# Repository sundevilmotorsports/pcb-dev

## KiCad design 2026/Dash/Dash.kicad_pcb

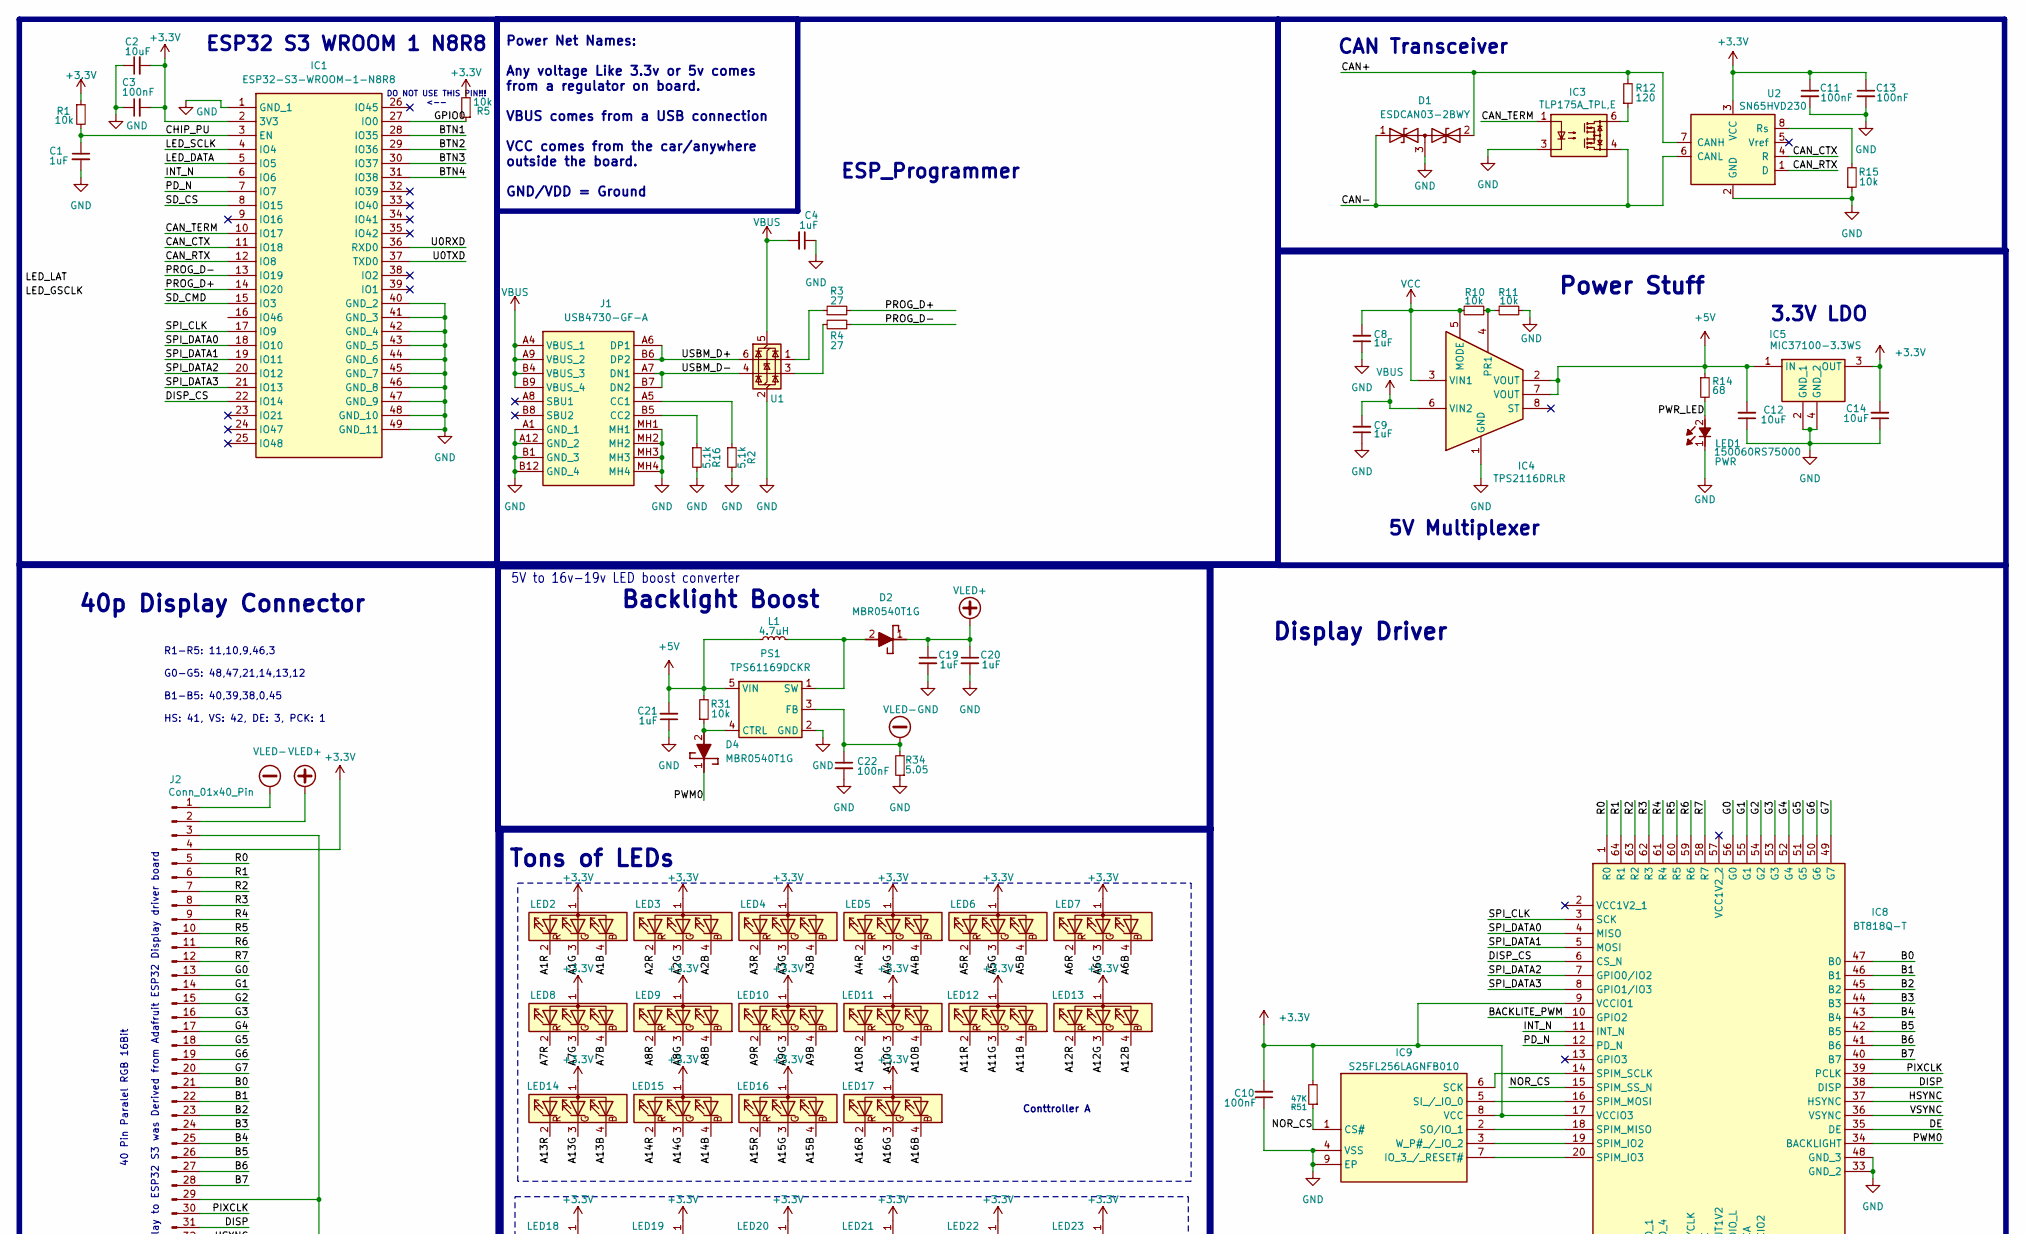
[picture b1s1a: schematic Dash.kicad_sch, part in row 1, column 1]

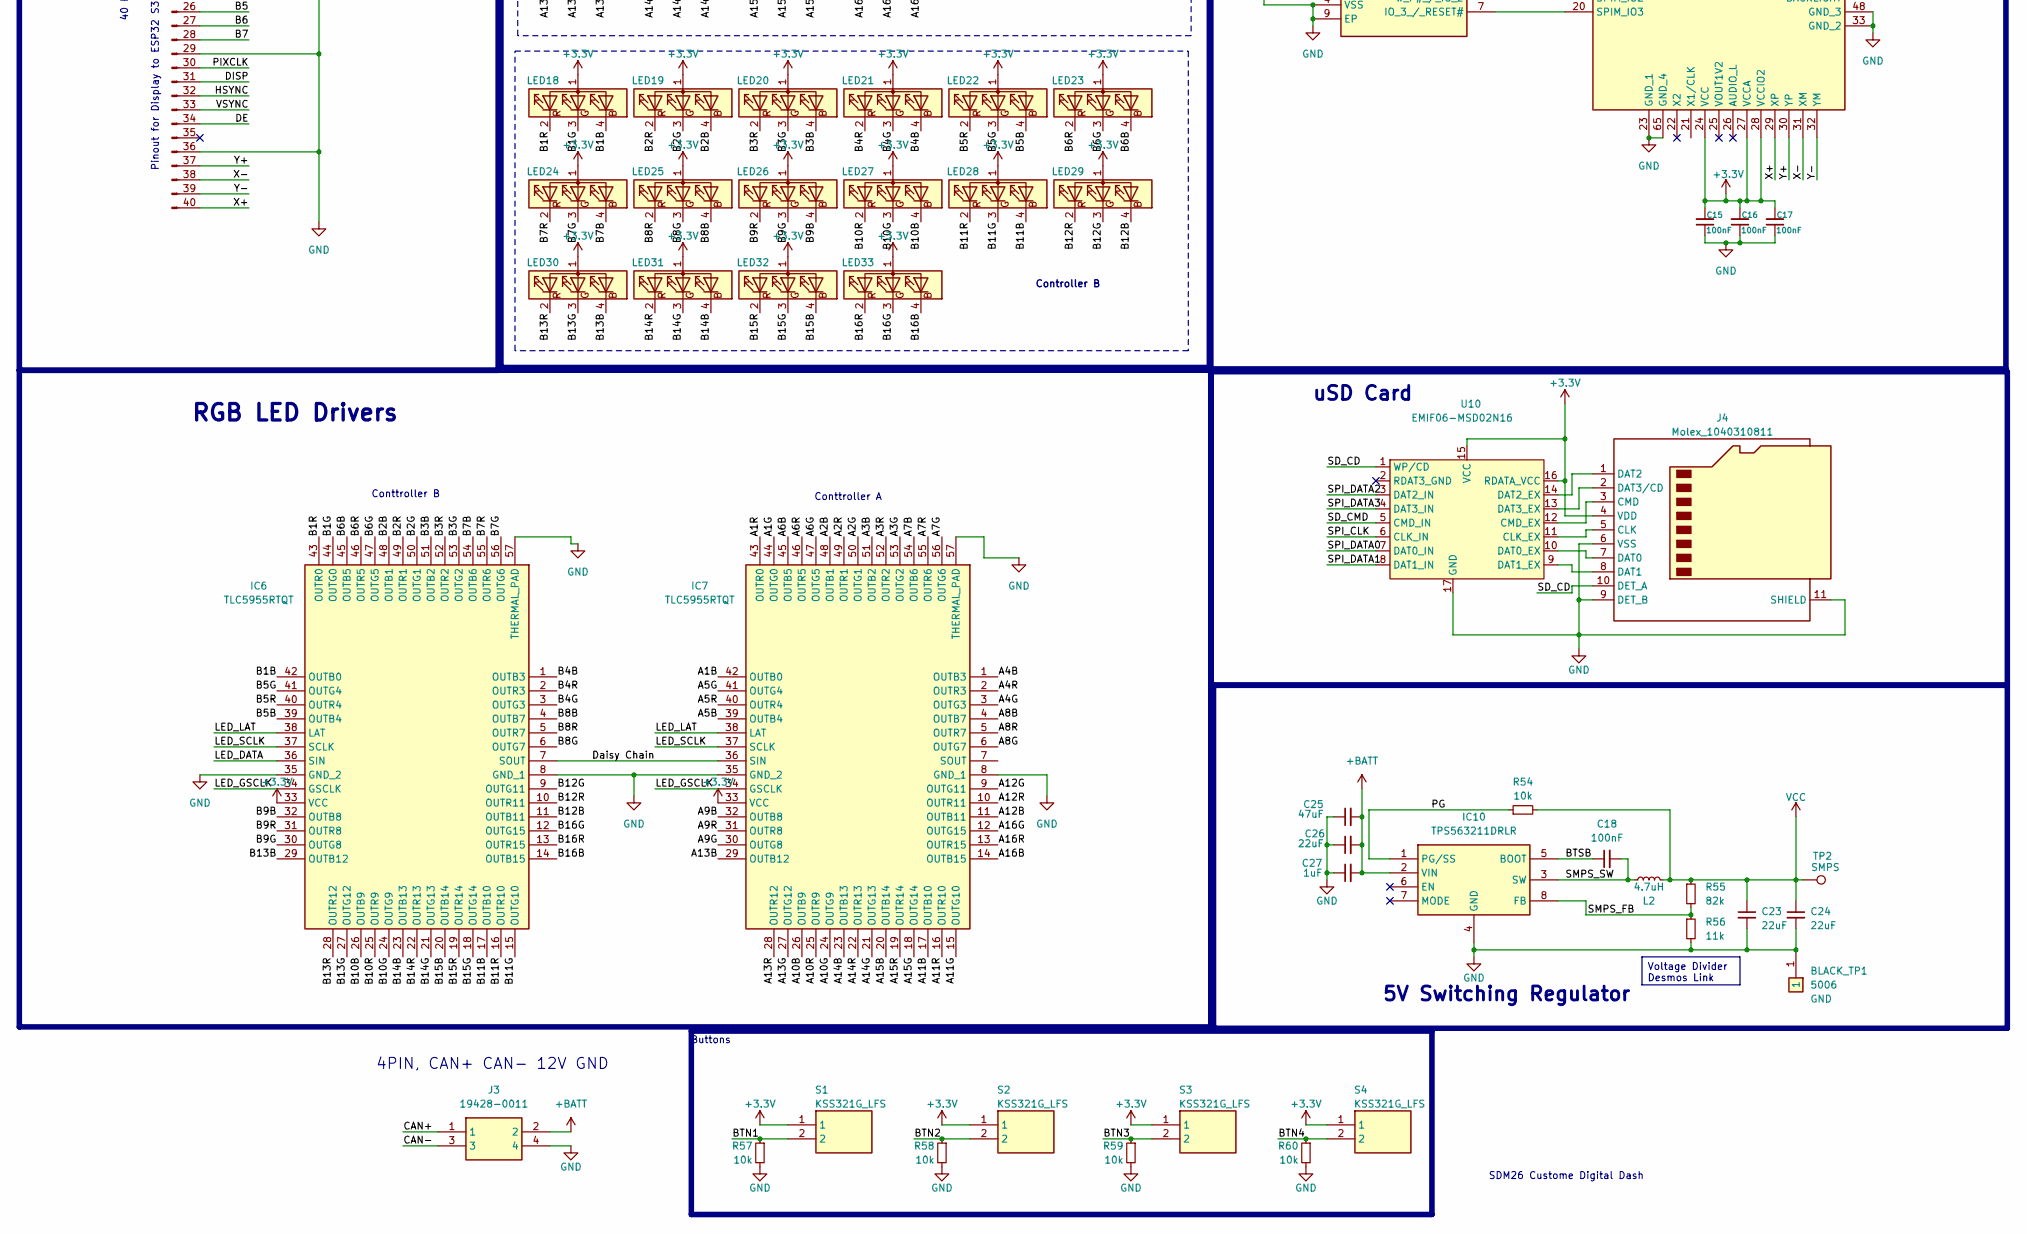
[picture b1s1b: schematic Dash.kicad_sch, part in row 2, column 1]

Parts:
BLACK_TP1: 5006; Mouser Part Number 534-5006
C1, C4, C8, C9, C19, C20, C21, C27: 1uF; C_0603_1608Metric
C2, C12, C14: 10uF; C_0603_1608Metric
C3, C10, C11, C13, C15, C16, C17, C18, C22: 100nF; C_0603_1608Metric
C23, C24, C26: 22uF; C_0603_1608Metric
C25: 47uF; CP_Elec_6.3x5.9
D1: ESDCAN03-2BWY; SOT65P210X110-3N; Mouser Part Number 511-ESDCAN03-2BWY
D2, D4: MBR0540T1G; SOD3716X135N; Mouser Part Number 863-MBR0540T1G
IC1: ESP32-S3-WROOM-1-N8R8; ESP32S3WROOM1N8R8; Mouser Part Number 356-EP32S3WROOM1N8R8
IC3: TLP175A_TPL,E; TLP266J; Mouser Part Number 757-TLP175A(TPLE
IC4: TPS2116DRLR; SOTFL50P160X60-8L; Mouser Part Number 595-TPS2116DRLR
IC5: MIC37100-3.3WS; SOT230P700X180-4N; Mouser Part Number 998-MIC37100-3.3WS
IC6, IC7: TLC5955RTQT; QFN50P800X800X100-57N-D; Mouser Part Number 595-TLC5955RTQT
IC8: BT818Q-T; QFN50P900X900X90-65N-D; Mouser Part Number 895-BT818Q-T
IC9: S25FL256LAGNFB010; SON127P600X500X80-9N-D; Mouser Part Number 727-S25FL256LANFB010
IC10: TPS563211DRLR; SOTFL50P160X60-8N; Mouser Part Number 595-TPS563211DRLR
J1: USB4730-GF-A; USB4730GFA; Mouser Part Number 640-USB4730GFA
J2: Conn_01x40_Pin; Omron_XF2M-4015-1A_1x40-1MP_P0.5mm_Horizontal
J3: 19428-0011; 194280011; Mouser Part Number 538-19428-0011
J4: Molex_1040310811; microSD_HC_Molex_104031-0811
L1: 4.7uH; BWVS006060454R7ML1
L2: 4.7uH; L_Bourns_SRP7028A_7.3x6.6mm
LED1: 150060RS75000; LEDC1608X80N; Mouser Part Number 710-150060RS75000
LED2, LED3, LED4, LED5, LED6, LED7, LED8, LED9, LED10, LED11, LED12, LED13, LED14, LED15, LED16, LED17, LED18, LED19, LED20, LED21, LED22, LED23, LED24, LED25, LED26, LED27, LED28, LED29, LED30, LED31, LED32, LED33: CLMUD-FKC-CHJNPM569ABB845343; PLCC4_CLMUD-FKC_CRW
PS1: TPS61169DCKR; SOT65P210X110-5N; Mouser Part Number 595-TPS61169DCKR
R1, R5, R10, R11, R15, R31, R54, R57, R58, R59, R60: 10k; R_0603_1608Metric
R2, R16: 5.1k; R_0603_1608Metric
R3, R4: 27; R_0603_1608Metric
R12: 120; R_0603_1608Metric
R14: 68; R_0603_1608Metric
R34: 5.05; R_0603_1608Metric
R51: 47K; R_0603_1608Metric
R55: 82k; R_0603_1608Metric
R56: 11k; R_0603_1608Metric
S1, S2, S3, S4: KSS321G_LFS; KSS321GLFS; Manufacturer_Part_Number KSS321G LFS
TP2: SMPS; TestPoint_Pad_1.5x1.5mm
U1: USBLC6-2SC6; SOT-23-6
U2: SN65HVD230; SOIC-8_3.9x4.9mm_P1.27mm
U10: EMIF06-MSD02N16; UQFN-17-3.5x1.2mm

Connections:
+3.3V: C2.2, C3.2, C10.2, C11.1, C13.1, C14.2, C15.2, C16.2, C17.2, IC1.2 (3V3), IC5.3 (OUT), IC6.33 (VCC), IC7.33 (VCC), IC8.9 (VCCIO1), IC8.17 (VCCIO3), IC8.24 (VCC), IC8.27 (VCCA), IC8.28 (VCCIO2), IC9.8 (VCC), J2.4, J4.4 (VDD), LED2.1 (A), LED3.1 (A), LED4.1 (A), LED5.1 (A), LED6.1 (A), LED7.1 (A), LED8.1 (A), LED9.1 (A), LED10.1 (A), LED11.1 (A), LED12.1 (A), LED13.1 (A), LED14.1 (A), LED15.1 (A), LED16.1 (A), LED17.1 (A), LED18.1 (A), LED19.1 (A), LED20.1 (A), LED21.1 (A), LED22.1 (A), LED23.1 (A), LED24.1 (A), LED25.1 (A), LED26.1 (A), LED27.1 (A), LED28.1 (A), LED29.1 (A), LED30.1 (A), LED31.1 (A), LED32.1 (A), LED33.1 (A), R1.1, R5.2, R51.2, S1.1, S2.1, S3.1, S4.1, U2.3 (VCC), U10.15 (VCC), U10.16 (RDATA_VCC)
+5V: C12.2, C21.2, IC4.2 (VOUT), IC4.7 (VOUT), IC5.1 (IN), L1.2, PS1.5 (VIN), R14.1, R31.2
+BATT: C25.2, C26.2, C27.2, IC10.2 (VIN), J3.2
/A1B: IC7.42 (OUTB0), LED2.4 (B)
/A1G: IC7.44 (OUTG0), LED2.3 (G)
/A1R: IC7.43 (OUTR0), LED2.2 (R)
/A2B: IC7.48 (OUTB1), LED3.4 (B)
/A2G: IC7.50 (OUTG1), LED3.3 (G)
/A2R: IC7.49 (OUTR1), LED3.2 (R)
/A3B: IC7.51 (OUTB2), LED4.4 (B)
/A3G: IC7.53 (OUTG2), LED4.3 (G)
/A3R: IC7.52 (OUTR2), LED4.2 (R)
/A4B: IC7.1 (OUTB3), LED5.4 (B)
/A4G: IC7.3 (OUTG3), LED5.3 (G)
/A4R: IC7.2 (OUTR3), LED5.2 (R)
/A5B: IC7.39 (OUTB4), LED6.4 (B)
/A5G: IC7.41 (OUTG4), LED6.3 (G)
/A5R: IC7.40 (OUTR4), LED6.2 (R)
/A6B: IC7.45 (OUTB5), LED7.4 (B)
/A6G: IC7.47 (OUTG5), LED7.3 (G)
/A6R: IC7.46 (OUTR5), LED7.2 (R)
/A7B: IC7.54 (OUTB6), LED8.4 (B)
/A7G: IC7.56 (OUTG6), LED8.3 (G)
/A7R: IC7.55 (OUTR6), LED8.2 (R)
/A8B: IC7.4 (OUTB7), LED9.4 (B)
/A8G: IC7.6 (OUTG7), LED9.3 (G)
/A8R: IC7.5 (OUTR7), LED9.2 (R)
/A9B: IC7.32 (OUTB8), LED10.4 (B)
/A9G: IC7.30 (OUTG8), LED10.3 (G)
/A9R: IC7.31 (OUTR8), LED10.2 (R)
/A10B: IC7.26 (OUTB9), LED11.4 (B)
/A10G: IC7.24 (OUTG9), LED11.3 (G)
/A10R: IC7.25 (OUTR9), LED11.2 (R)
/A11B: IC7.17 (OUTB10), LED12.4 (B)
/A11G: IC7.15 (OUTG10), LED12.3 (G)
/A11R: IC7.16 (OUTR10), LED12.2 (R)
/A12B: IC7.11 (OUTB11), LED13.4 (B)
/A12G: IC7.9 (OUTG11), LED13.3 (G)
/A12R: IC7.10 (OUTR11), LED13.2 (R)
/A13B: IC7.29 (OUTB12), LED14.4 (B)
/A13G: IC7.27 (OUTG12), LED14.3 (G)
/A13R: IC7.28 (OUTR12), LED14.2 (R)
/A14B: IC7.23 (OUTB13), LED15.4 (B)
/A14G: IC7.21 (OUTG13), LED15.3 (G)
/A14R: IC7.22 (OUTR13), LED15.2 (R)
/A15B: IC7.20 (OUTB14), LED16.4 (B)
/A15G: IC7.18 (OUTG14), LED16.3 (G)
/A15R: IC7.19 (OUTR14), LED16.2 (R)
/A16B: IC7.14 (OUTB15), LED17.4 (B)
/A16G: IC7.12 (OUTG15), LED17.3 (G)
/A16R: IC7.13 (OUTR15), LED17.2 (R)
/B0: IC8.47 (B0), J2.21
/B1: IC8.46 (B1), J2.22
/B1B: IC6.42 (OUTB0), LED18.4 (B)
/B1G: IC6.44 (OUTG0), LED18.3 (G)
/B1R: IC6.43 (OUTR0), LED18.2 (R)
/B2: IC8.45 (B2), J2.23
/B2B: IC6.48 (OUTB1), LED19.4 (B)
/B2G: IC6.50 (OUTG1), LED19.3 (G)
/B2R: IC6.49 (OUTR1), LED19.2 (R)
/B3: IC8.44 (B3), J2.24
/B3B: IC6.51 (OUTB2), LED20.4 (B)
/B3G: IC6.53 (OUTG2), LED20.3 (G)
/B3R: IC6.52 (OUTR2), LED20.2 (R)
/B4: IC8.43 (B4), J2.25
/B4B: IC6.1 (OUTB3), LED21.4 (B)
/B4G: IC6.3 (OUTG3), LED21.3 (G)
/B4R: IC6.2 (OUTR3), LED21.2 (R)
/B5: IC8.42 (B5), J2.26
/B5B: IC6.39 (OUTB4), LED22.4 (B)
/B5G: IC6.41 (OUTG4), LED22.3 (G)
/B5R: IC6.40 (OUTR4), LED22.2 (R)
/B6: IC8.41 (B6), J2.27
/B6B: IC6.45 (OUTB5), LED23.4 (B)
/B6G: IC6.47 (OUTG5), LED23.3 (G)
/B6R: IC6.46 (OUTR5), LED23.2 (R)
/B7: IC8.40 (B7), J2.28
/B7B: IC6.54 (OUTB6), LED24.4 (B)
/B7G: IC6.56 (OUTG6), LED24.3 (G)
/B7R: IC6.55 (OUTR6), LED24.2 (R)
/B8B: IC6.4 (OUTB7), LED25.4 (B)
/B8G: IC6.6 (OUTG7), LED25.3 (G)
/B8R: IC6.5 (OUTR7), LED25.2 (R)
/B9B: IC6.32 (OUTB8), LED26.4 (B)
/B9G: IC6.30 (OUTG8), LED26.3 (G)
/B9R: IC6.31 (OUTR8), LED26.2 (R)
/B10B: IC6.26 (OUTB9), LED27.4 (B)
/B10G: IC6.24 (OUTG9), LED27.3 (G)
/B10R: IC6.25 (OUTR9), LED27.2 (R)
/B11B: IC6.17 (OUTB10), LED28.4 (B)
/B11G: IC6.15 (OUTG10), LED28.3 (G)
/B11R: IC6.16 (OUTR10), LED28.2 (R)
/B12B: IC6.11 (OUTB11), LED29.4 (B)
/B12G: IC6.9 (OUTG11), LED29.3 (G)
/B12R: IC6.10 (OUTR11), LED29.2 (R)
/B13B: IC6.29 (OUTB12), LED30.4 (B)
/B13G: IC6.27 (OUTG12), LED30.3 (G)
/B13R: IC6.28 (OUTR12), LED30.2 (R)
/B14B: IC6.23 (OUTB13), LED31.4 (B)
/B14G: IC6.21 (OUTG13), LED31.3 (G)
/B14R: IC6.22 (OUTR13), LED31.2 (R)
/B15B: IC6.20 (OUTB14), LED32.4 (B)
/B15G: IC6.18 (OUTG14), LED32.3 (G)
/B15R: IC6.19 (OUTR14), LED32.2 (R)
/B16B: IC6.14 (OUTB15), LED33.4 (B)
/B16G: IC6.12 (OUTG15), LED33.3 (G)
/B16R: IC6.13 (OUTR15), LED33.2 (R)
/BACKLITE_PWM: IC8.10 (GPIO2)
/BTN1: IC1.28 (IO35), R57.1, S1.2
/BTN2: IC1.29 (IO36), R58.1, S2.2
/BTN3: IC1.30 (IO37), R59.1, S3.2
/BTN4: IC1.31 (IO38), R60.1, S4.2
/BTSB: C18.1, IC10.5 (BOOT)
/CAN+: D1.2, J3.1, R12.2, U2.7 (CANH)
/CAN-: D1.1, IC3.4, J3.3, U2.6 (CANL)
/CAN_CTX: IC1.11 (IO18), U2.4 (R)
/CAN_RTX: IC1.12 (IO8), U2.1 (D)
/CAN_TERM: IC1.10 (IO17), IC3.1
/CHIP_PU: C1.1, IC1.3 (EN), R1.2
/DE: IC8.35 (DE), J2.34
/DISP: IC8.38 (DISP), J2.31
/DISP_CS: IC1.22 (IO14), IC8.6 (CS_N)
/Daisy Chain: IC6.7 (SOUT), IC7.36 (SIN)
/G0: IC8.56 (G0), J2.13
/G1: IC8.55 (G1), J2.14
/G2: IC8.54 (G2), J2.15
/G3: IC8.53 (G3), J2.16
/G4: IC8.52 (G4), J2.17
/G5: IC8.51 (G5), J2.18
/G6: IC8.50 (G6), J2.19
/G7: IC8.49 (G7), J2.20
/GPIO0: IC1.27 (IO0), R5.1
/HSYNC: IC8.37 (HSYNC), J2.32
/INT_N: IC1.6 (IO6), IC8.11 (INT_N)
/LED_DATA: IC1.5 (IO5), IC6.36 (SIN)
/LED_GSCLK: IC6.34 (GSCLK), IC7.34 (GSCLK)
/LED_LAT: IC6.38 (LAT), IC7.38 (LAT)
/LED_SCLK: IC1.4 (IO4), IC6.37 (SCLK), IC7.37 (SCLK)
/NOR_CS: IC8.15 (SPIM_SS_N), IC9.1 (CS#), R51.1
/PD_N: IC1.7 (IO7), IC8.12 (PD_N)
/PG: IC10.1 (PG/SS), R54.1
/PIXCLK: IC8.39 (PCLK), J2.30
/PROG_D+: IC1.14 (IO20), R3.2
/PROG_D-: IC1.13 (IO19), R4.1
/PWM0: D4.1 (K), IC8.34 (BACKLIGHT)
/PWR_LED: LED1.2 (A), R14.2
/R0: IC8.1 (R0), J2.5
/R1: IC8.64 (R1), J2.6
/R2: IC8.63 (R2), J2.7
/R3: IC8.62 (R3), J2.8
/R4: IC8.61 (R4), J2.9
/R5: IC8.60 (R5), J2.10
/R6: IC8.59 (R6), J2.11
/R7: IC8.58 (R7), J2.12
/SD_CD: J4.10 (DET_A), U10.1 (WP/CD)
/SD_CMD: IC1.15 (IO3), U10.5 (CMD_IN)
/SD_CS: IC1.8 (IO15)
/SMPS_FB: IC10.8 (FB), R55.2, R56.1
/SMPS_SW: C18.2, IC10.3 (SW), L2.2
/SPI_CLK: IC1.17 (IO9), IC8.3 (SCK), U10.6 (CLK_IN)
/SPI_DATA0: IC1.18 (IO10), IC8.4 (MISO), U10.7 (DAT0_IN)
/SPI_DATA1: IC1.19 (IO11), IC8.5 (MOSI), U10.8 (DAT1_IN)
/SPI_DATA2: IC1.20 (IO12), IC8.7 (GPIO0/IO2), U10.3 (DAT2_IN)
/SPI_DATA3: IC1.21 (IO13), IC8.8 (GPIO1/IO3), U10.4 (DAT3_IN)
/U0RXD: IC1.36 (RXD0)
/U0TXD: IC1.37 (TXD0)
/USBM_D+: J1.A6 (DP1), J1.B6 (DP2), U1.6 (I/O1)
/USBM_D-: J1.A7 (DN1), J1.B7 (DN2), U1.4 (I/O2)
/VSYNC: IC8.36 (VSYNC), J2.33
/X+: IC8.29 (XP), J2.40
/X-: IC8.31 (XM), J2.38
/Y+: IC8.30 (YP), J2.37
/Y-: IC8.32 (YM), J2.39
GND: BLACK_TP1.1 (1_1), C1.2, C2.1, C3.1, C4.1, C8.1, C9.1, C10.1, C11.2, C12.1, C13.2, C14.1, C15.1, C16.1, C17.1, C19.2, C20.2, C21.1, C22.2, C23.2, C24.2, C25.1, C26.1, C27.1, D1.3, IC1.1 (GND_1), IC1.40 (GND_2), IC1.41 (GND_3), IC1.42 (GND_4), IC1.43 (GND_5), IC1.44 (GND_6), IC1.45 (GND_7), IC1.46 (GND_8), IC1.47 (GND_9), IC1.48 (GND_10), IC1.49 (GND_11), IC3.3, IC4.1 (GND), IC5.2 (GND_1), IC5.4 (GND_2), IC6.8 (GND_1), IC6.35 (GND_2), IC6.57 (THERMAL_PAD), IC7.8 (GND_1), IC7.35 (GND_2), IC7.57 (THERMAL_PAD), IC8.23 (GND_1), IC8.33 (GND_2), IC8.48 (GND_3), IC8.65 (GND_4), IC9.4 (VSS), IC9.9 (EP), IC10.4 (GND), J1.A1 (GND_1), J1.A12 (GND_2), J1.B1 (GND_3), J1.B12 (GND_4), J1.MH1, J1.MH2, J1.MH3, J1.MH4, J2.3, J2.29, J2.36, J3.4, J4.6 (VSS), J4.9 (DET_B), J4.11 (SHIELD), LED1.1 (K), PS1.2 (GND), R2.2, R11.1, R15.1, R16.2, R34.1, R56.2, R57.2, R58.2, R59.2, R60.2, U1.2 (GND), U2.2 (GND), U10.17 (GND)
unnamed: D2.2 (A), L1.1, PS1.1 (SW)
unnamed: D4.2 (A), PS1.4 (CTRL), R31.1
unnamed: IC3.6, R12.1
unnamed: IC4.4 (PR1), R10.1, R11.2
unnamed: IC8.19 (SPIM_IO2), IC9.3 (W_P#_/_IO_2)
unnamed: IC8.20 (SPIM_IO3), IC9.7 (IO_3_/_RESET#)
unnamed: IC8.18 (SPIM_MISO), IC9.2 (SO/IO_1)
unnamed: IC8.16 (SPIM_MOSI), IC9.5 (SI_/_IO_0)
unnamed: IC8.14 (SPIM_SCLK), IC9.6 (SCK)
unnamed: J1.A5 (CC1), R2.1
unnamed: J1.B5 (CC2), R16.1
unnamed: J4.5 (CLK), U10.11 (CLK_EX)
unnamed: J4.3 (CMD), U10.12 (CMD_EX)
unnamed: J4.7 (DAT0), U10.10 (DAT0_EX)
unnamed: J4.8 (DAT1), U10.9 (DAT1_EX)
unnamed: J4.1 (DAT2), U10.14 (DAT2_EX)
unnamed: J4.2 (DAT3/CD), U10.13 (DAT3_EX)
unnamed: R3.1, U1.1 (I/O1)
unnamed: R4.2, U1.3 (I/O2)
unnamed: R15.2, U2.8 (Rs)
VBUS: C4.2, C9.2, IC4.6 (VIN2), J1.A4 (VBUS_1), J1.A9 (VBUS_2), J1.B4 (VBUS_3), J1.B9 (VBUS_4), U1.5 (VBUS)
VCC: C8.2, C23.1, C24.1, IC4.3 (VIN1), IC4.5 (MODE), L2.1, R10.2, R54.2, R55.1, TP2.1 (1_1)
VLED+: C19.1, C20.1, D2.1 (K), J2.2
VLED-: C22.1, J2.1, PS1.3 (FB), R34.2

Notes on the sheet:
Pinout for Display to ESP32 S3 was Derived from Adafruit ESP32 Display driver board
Controller B
CAN Transceiver
R1-R5: 11,10,9,46,3 G0-G5: 48,47,21,14,13,12 B1-B5: 40,39,38,0,45 HS: 41, VS: 42, DE: 3, PCK: 1
RGB LED Drivers
3.3V LDO
40 Pin Paralel RGB 16Bit
Display Driver
Conttroller A
5V Multiplexer
Buttons
40p Display Connector
5V to 16v-19v LED boost converter
ESP32 S3 WROOM 1 N8R8
DO NOT USE THIS PIN!!! <--
ESP_Programmer
Power Net Names: Any voltage Like 3.3v or 5v comes from a regulator on board. VBUS comes from a USB connection VCC comes from the car/anywhere outside the board. GND/VDD = Ground
5V Switching Regulator
Power Stuff
SDM26 Custome Digital Dash
Tons of LEDs
uSD Card
Conttroller B
Backlight Boost
4PIN, CAN+ CAN- 12V GND
Voltage Divider Desmos Link

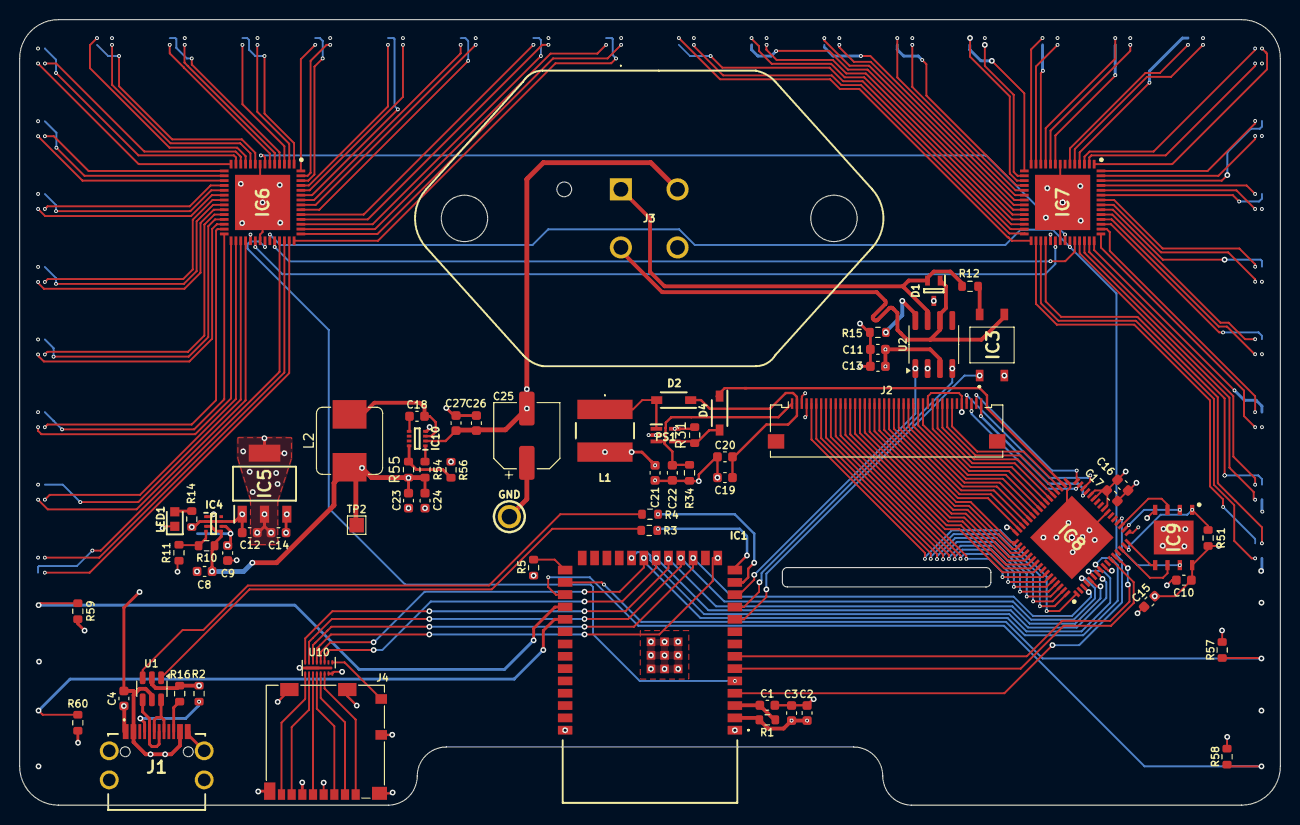
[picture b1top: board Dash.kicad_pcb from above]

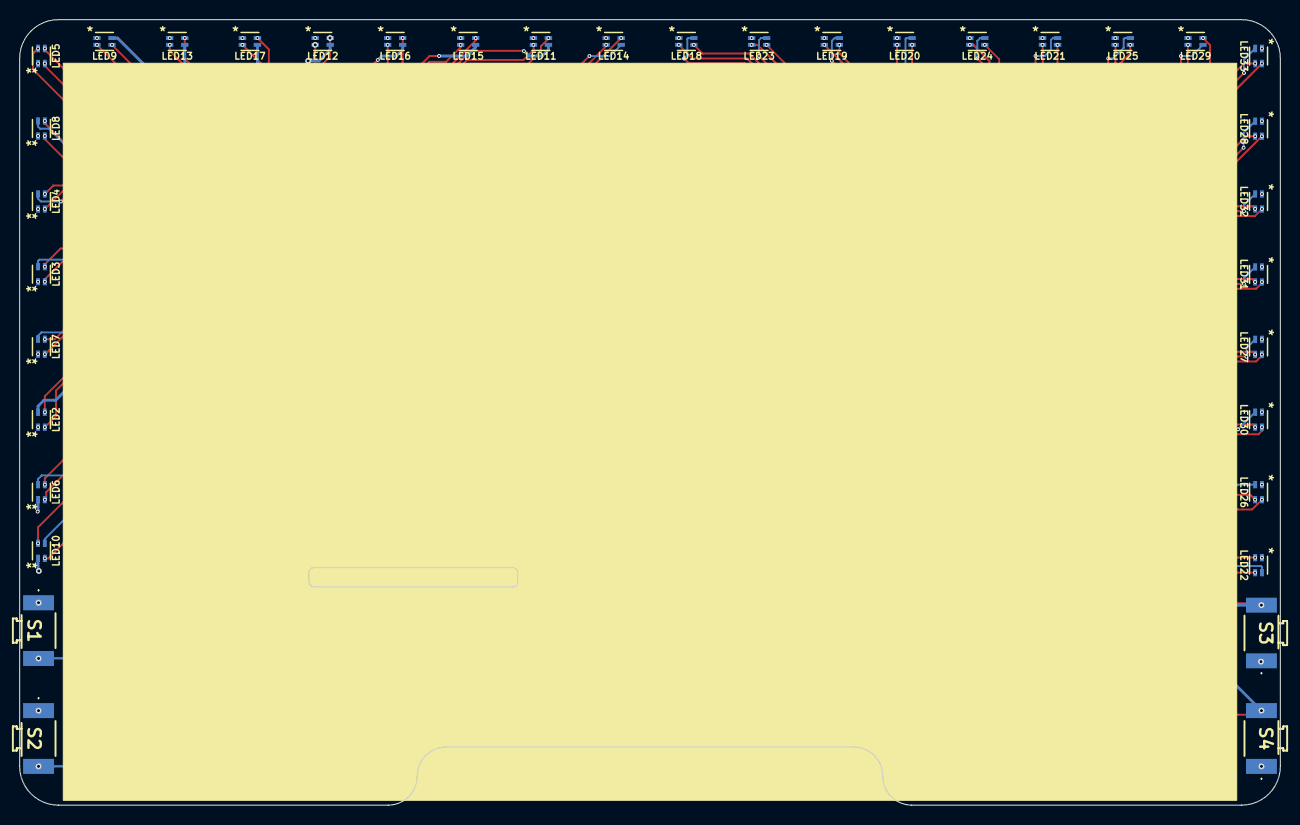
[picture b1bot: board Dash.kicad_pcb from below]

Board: 4 copper layers, 130.0 x 81.0 mm, 106 parts (36 on the bottom side), 194 nets.

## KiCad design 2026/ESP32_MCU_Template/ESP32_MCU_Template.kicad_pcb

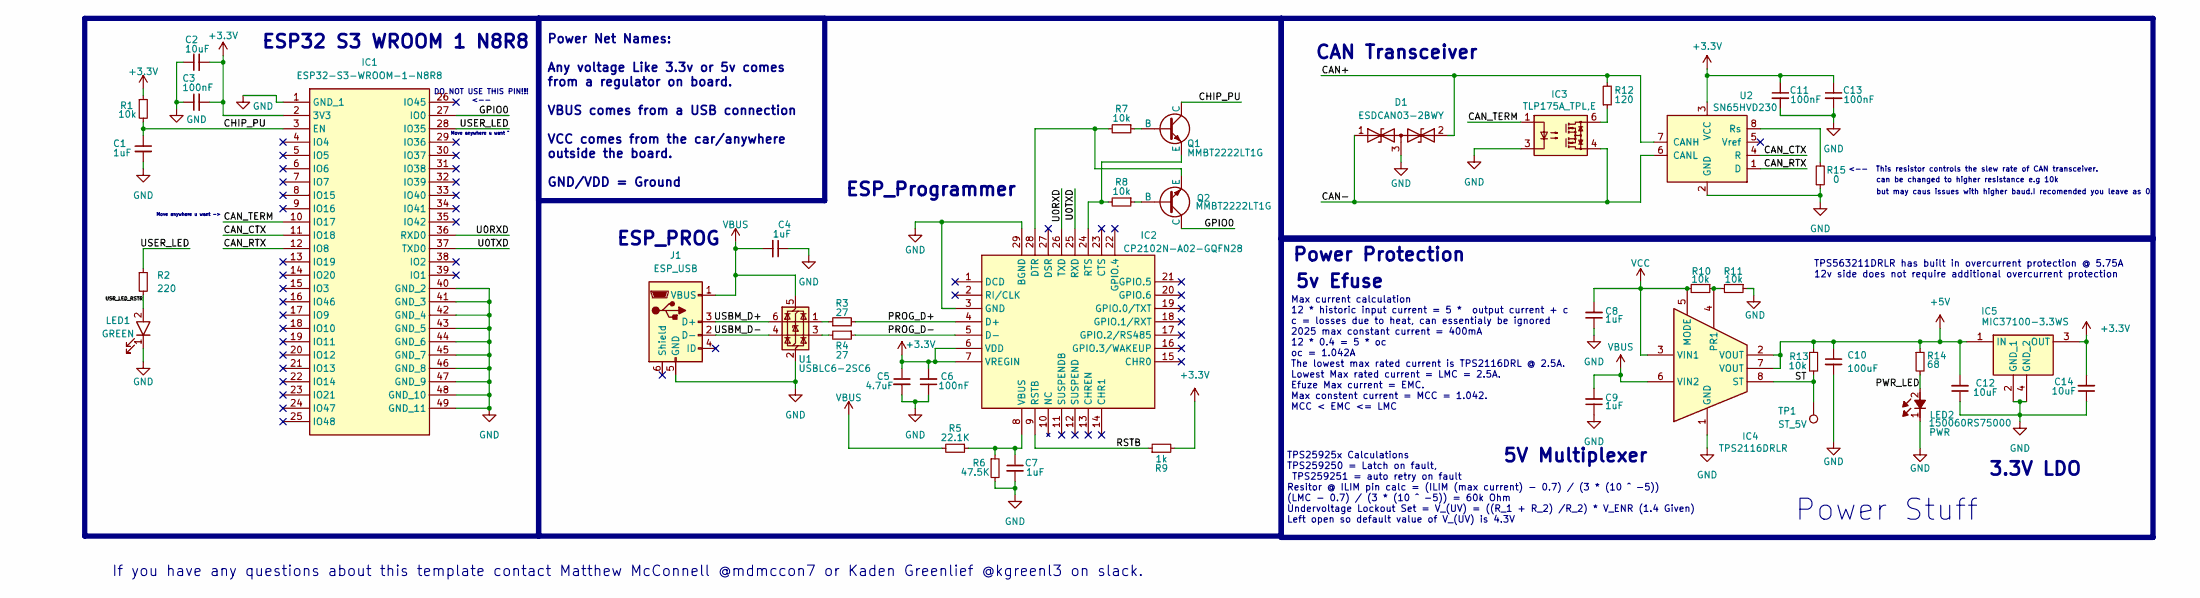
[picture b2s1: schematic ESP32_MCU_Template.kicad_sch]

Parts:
C1, C4, C7, C8, C9: 1uF; C_0603_1608Metric
C2, C12, C14: 10uF; C_0603_1608Metric
C3, C6, C11, C13: 100nF; C_0603_1608Metric
C5: 4.7uF; C_0603_1608Metric
C10: 100uF; C_0603_1608Metric
D1: ESDCAN03-2BWY; SOT65P210X110-3N; Mouser Part Number 511-ESDCAN03-2BWY
IC1: ESP32-S3-WROOM-1-N8R8; ESP32S3WROOM1N8R8; Mouser Part Number 356-EP32S3WROOM1N8R8
IC2: CP2102N-A02-GQFN28; QFN50P500X500X80-29N-D; Mouser Part Number 634-CP2102NA02GQFN28
IC3: TLP175A_TPL,E; TLP266J; Mouser Part Number 757-TLP175A(TPLE
IC4: TPS2116DRLR; SOTFL50P160X60-8L; Mouser Part Number 595-TPS2116DRLR
IC5: MIC37100-3.3WS; SOT230P700X180-4N; Mouser Part Number 998-MIC37100-3.3WS
J1: ESP_USB; USB_Micro-B_Molex-105017-0001
LED1: GREEN; LED_0603_1608Metric; Mouser Part Number 720-P4112S2U1252X4X5
LED2: 150060RS75000; LEDC1608X80N; Mouser Part Number 710-150060RS75000
Q1, Q2: MMBT2222LT1G; SOT96P237X111-3N
R1, R7, R8, R10, R11, R13: 10k; R_0603_1608Metric
R2: 220; R_0603_1608Metric
R3, R4: 27; R_0603_1608Metric
R5: 22.1K; R_0603_1608Metric
R6: 47.5K; R_0603_1608Metric
R9: 1k; R_0603_1608Metric
R12: 120; R_0603_1608Metric
R14: 68; R_0603_1608Metric
R15: 0; R_0603_1608Metric
TP1: ST_5V; TestPoint_Pad_1.5x1.5mm
U1: USBLC6-2SC6; SOT-23-6
U2: SN65HVD230; SOIC-8_3.9x4.9mm_P1.27mm

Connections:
+3.3V: C2.2, C3.2, C5.1, C6.2, C11.1, C13.1, C14.2, IC1.2 (3V3), IC2.6 (VDD), IC2.7 (VREGIN), IC5.3 (OUT), R1.1, R9.2, U2.3 (VCC)
+5V: C10.1, C12.2, IC4.2 (VOUT), IC4.7 (VOUT), IC5.1 (IN), R13.1, R14.1
/CAN+: D1.2, R12.2, U2.7 (CANH)
/CAN-: D1.1, IC3.4, U2.6 (CANL)
/CAN_CTX: IC1.11 (IO18), U2.4 (R)
/CAN_RTX: IC1.12 (IO8), U2.1 (D)
/CAN_TERM: IC1.10 (IO17), IC3.1
/CHIP_PU: C1.1, IC1.3 (EN), Q1.3 (C), R1.2
/GPIO0: IC1.27 (IO0), Q2.3 (C)
/PROG_D+: IC2.4 (D+), R3.2
/PROG_D-: IC2.5 (D-), R4.1
/PWR_LED: LED2.2 (A), R14.2
/RSTB: IC2.9 (RSTB), R9.1
/ST: IC4.8 (ST), R13.2, TP1.1
/U0RXD: IC1.36 (RXD0), IC2.26 (TXD)
/U0TXD: IC1.37 (TXD0), IC2.25 (RXD)
/USBM_D+: J1.3 (D+), U1.6 (I/O1)
/USBM_D-: J1.2 (D-), U1.4 (I/O2)
/USER_LED: IC1.28 (IO35), R2.1
/USR_LED_RSTR: LED1.2 (A), R2.2
GND: C1.2, C2.1, C3.1, C4.1, C5.2, C6.1, C7.2, C8.1, C9.1, C10.2, C11.2, C12.1, C13.2, C14.1, D1.3, IC1.1 (GND_1), IC1.40 (GND_2), IC1.41 (GND_3), IC1.42 (GND_4), IC1.43 (GND_5), IC1.44 (GND_6), IC1.45 (GND_7), IC1.46 (GND_8), IC1.47 (GND_9), IC1.48 (GND_10), IC1.49 (GND_11), IC2.3 (GND), IC2.29 (BGND), IC3.3, IC4.1 (GND), IC5.2 (GND_1), IC5.4 (GND_2), J1.5 (GND), LED1.1 (K), LED2.1 (K), R6.2, R11.1, R15.1, U1.2 (GND), U2.2 (GND)
unnamed: IC2.28 (DTR), Q2.2 (E), R7.2
unnamed: IC2.24 (RTS), Q1.2 (E), R8.2
unnamed: C7.1, IC2.8 (VBUS), R5.1, R6.1
unnamed: IC3.6, R12.1
unnamed: IC4.4 (PR1), R10.1, R11.2
unnamed: Q1.1 (B), R7.1
unnamed: Q2.1 (B), R8.1
unnamed: R3.1, U1.1 (I/O1)
unnamed: R4.2, U1.3 (I/O2)
unnamed: R15.2, U2.8 (Rs)
VBUS: C4.2, C9.2, IC4.6 (VIN2), J1.1 (VBUS), R5.2, U1.5 (VBUS)
VCC: C8.2, IC4.3 (VIN1), IC4.5 (MODE), R10.2

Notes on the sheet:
<-- This resistor controls the slew rate of CAN transceiver.
If you have any questions about this template contact Matthew McConnell @mdmccon7 or Kaden Greenlief @kgreenl3 on slack.
Move anywhere u want ^
Power Protection
Power Stuff
3.3V LDO
TPS563211DRLR has built in overcurrent protection @ 5.75A 12v side does not require additional overcurrent protection
Move anywhere u want ->
5v Efuse
but may caus issues with higher baud.I recomended you leave as 0.
TPS25925x Calculations TPS259250 = Latch on fault, TPS259251 = auto retry on fault Resitor @ ILIM pin calc = (ILIM (max current) - 0.7) / (3 * (10 ^ -5)) (LMC - 0.7) / (3 * (10 ^ -5)) = 60k Ohm Undervoltage Lockout Set = V_(UV) = ((R_1 + R_2) /R_2) * V_ENR (1.4 Given) Left open so default value of 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
ESP_PROG
CAN Transceiver
5V Multiplexer
DO NOT USE THIS PIN!!! <--
can be changed to higher resistance e.g 10k
Max current calculation 12 * historic input current = 5 * output current + c c = losses due to heat, can essentialy be ignored 2025 max constant current = 400mA 12 * 0.4 = 5 * oc oc = 1.042A The lowest max rated current is TPS2116DRL @ 2.5A. Lowest Max rated current = LMC = 2.5A. Efuze Max current 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
ESP32 S3 WROOM 1 N8R8
ESP_Programmer
Power Net Names: Any voltage Like 3.3v or 5v comes from a regulator on board. VBUS comes from a USB connection VCC comes from the car/anywhere outside the board. GND/VDD = Ground

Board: 2 copper layers, 43 parts (0 on the bottom side), 33 nets, no tracks yet.

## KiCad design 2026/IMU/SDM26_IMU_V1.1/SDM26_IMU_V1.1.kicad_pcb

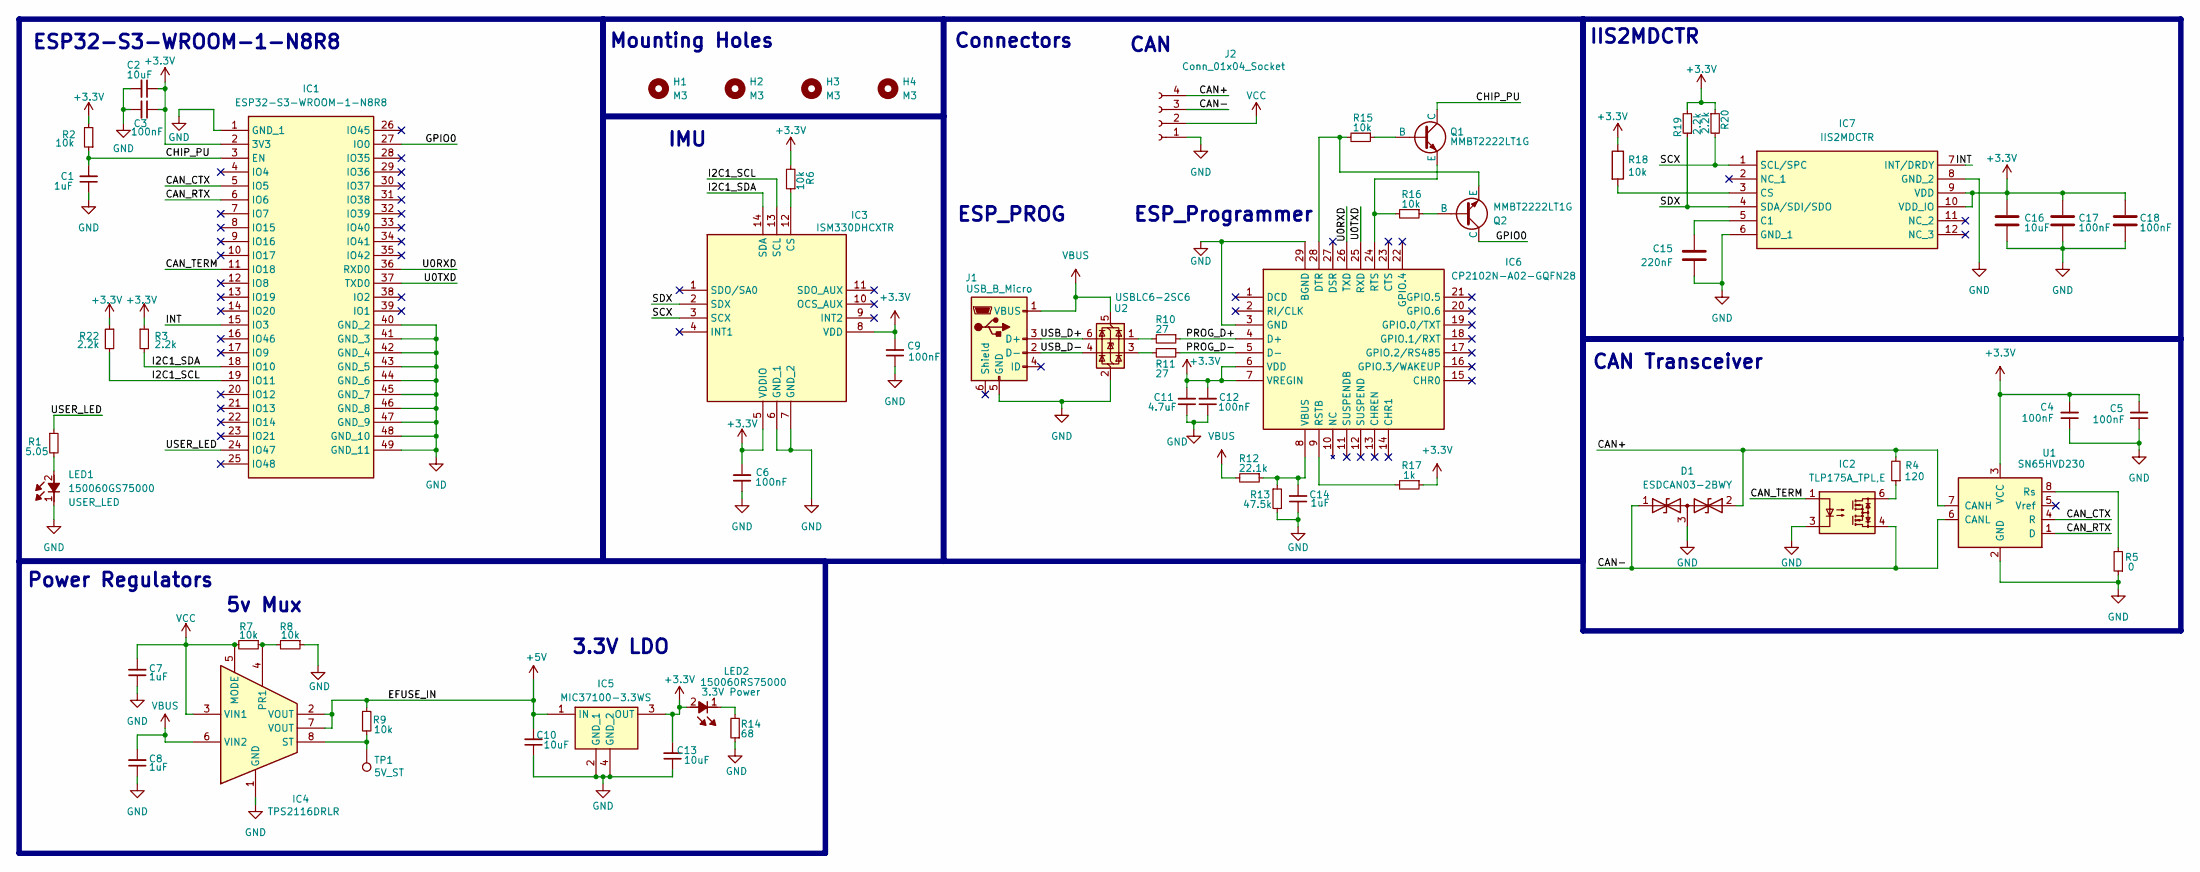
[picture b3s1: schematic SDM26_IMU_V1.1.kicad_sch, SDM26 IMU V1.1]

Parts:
C1, C7, C8, C14: 1uF; C_0603_1608Metric
C2, C10, C13, C16: 10uF; C_0603_1608Metric
C3, C4, C5, C6, C9, C12, C17, C18: 100nF; C_0603_1608Metric
C11: 4.7uF; C_0603_1608Metric
C15: 220nF; C_0603_1608Metric
D1: ESDCAN03-2BWY; SOT65P210X110-3N; Mouser Part Number 511-ESDCAN03-2BWY
H1, H2, H3, H4: M3; MountingHole_3.2mm_M3
IC1: ESP32-S3-WROOM-1-N8R8; ESP32S3WROOM1N8R8; Mouser Part Number 356-EP32S3WROOM1N8R8
IC2: TLP175A_TPL,E; TLP266J; Mouser Part Number 757-TLP175A(TPLE
IC3: ISM330DHCXTR; LSM6DS3USTR; Mouser Part Number 511-ISM330DHCXTR
IC4: TPS2116DRLR; SOTFL50P160X60-8L; Mouser Part Number 595-TPS2116DRLR
IC5: MIC37100-3.3WS; SOT230P700X180-4N; Mouser Part Number 998-MIC37100-3.3WS
IC6: CP2102N-A02-GQFN28; QFN50P500X500X80-29N-D; Mouser Part Number 634-CP2102NA02GQFN28
IC7: IIS2MDCTR; Mouser Part Number 511-IIS2MDCTR
J1: USB_B_Micro; USB_Micro-B_Molex-105017-0001
J2: Conn_01x04_Socket; JST_XH_S4B-XH-A_1x04_P2.50mm_Horizontal
LED1: 150060GS75000; LEDC1608X80N; Mouser Part Number 710-150060VS75000
LED2: 150060RS75000; LEDC1608X80N; Mouser Part Number 710-150060RS75000
Q1, Q2: MMBT2222LT1G; SOT96P237X111-3N
R1: 5.05; R_0603_1608Metric
R2, R6, R7, R8, R9, R15, R16, R18: 10k; R_0603_1608Metric
R3, R19, R20, R22: 2.2k; R_0603_1608Metric
R4: 120; R_0603_1608Metric
R5: 0; R_0603_1608Metric
R10, R11: 27; R_0603_1608Metric
R12: 22.1k; R_0603_1608Metric
R13: 47.5k; R_0603_1608Metric
R14: 68; R_0603_1608Metric
R17: 1k; R_0603_1608Metric
TP1: 5V_ST; TestPoint_Pad_1.5x1.5mm
U1: SN65HVD230; SOIC-8_3.9x4.9mm_P1.27mm
U2: USBLC6-2SC6; SOT-23-6

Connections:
+3.3V: C2.1, C3.1, C4.2, C5.2, C6.2, C9.2, C11.2, C12.2, C13.2, C16.1, C17.1, C18.1, IC1.2 (3V3), IC3.5 (VDDIO), IC3.8 (VDD), IC5.3 (OUT), IC6.6 (VDD), IC6.7 (VREGIN), IC7.9 (VDD), IC7.10 (VDD_IO), LED2.2 (A), R2.2, R3.1, R6.2, R17.1, R18.1, R19.2, R20.1, R22.1, U1.3 (VCC)
+5V: C10.2, IC4.2 (VOUT), IC4.7 (VOUT), IC5.1 (IN), R9.1
/CAN+: D1.2, J2.4, R4.2, U1.7 (CANH)
/CAN-: D1.1, IC2.4, J2.3, U1.6 (CANL)
/CAN_CTX: IC1.5 (IO5), U1.4 (R)
/CAN_RTX: IC1.6 (IO6), U1.1 (D)
/CAN_TERM: IC1.11 (IO18), IC2.1
/CHIP_PU: C1.2, IC1.3 (EN), Q1.3 (C), R2.1
/GPIO0: IC1.27 (IO0), Q2.3 (C)
/I2C1_SCL: IC1.19 (IO11), IC3.13 (SCL), R22.2
/I2C1_SDA: IC1.18 (IO10), IC3.14 (SDA), R3.2
/INT: IC1.15 (IO3), IC7.7 (INT/DRDY)
/PROG_D+: IC6.4 (D+), R10.1
/PROG_D-: IC6.5 (D-), R11.1
/SCX: IC3.3 (SCX), IC7.1 (SCL/SPC), R20.2
/SDX: IC3.2 (SDX), IC7.4 (SDA/SDI/SDO), R19.1
/U0RXD: IC1.36 (RXD0), IC6.26 (TXD)
/U0TXD: IC1.37 (TXD0), IC6.25 (RXD)
/USB_D+: J1.3 (D+), U2.6 (I/O1)
/USB_D-: J1.2 (D-), U2.4 (I/O2)
/USER_LED: IC1.24 (IO47), R1.1
GND: C1.1, C2.2, C3.2, C4.1, C5.1, C6.1, C7.1, C8.1, C9.1, C10.1, C11.1, C12.1, C13.1, C14.1, C15.2, C16.2, C17.2, C18.2, D1.3, IC1.1 (GND_1), IC1.40 (GND_2), IC1.41 (GND_3), IC1.42 (GND_4), IC1.43 (GND_5), IC1.44 (GND_6), IC1.45 (GND_7), IC1.46 (GND_8), IC1.47 (GND_9), IC1.48 (GND_10), IC1.49 (GND_11), IC2.3, IC3.6 (GND_1), IC3.7 (GND_2), IC4.1 (GND), IC5.2 (GND_1), IC5.4 (GND_2), IC6.3 (GND), IC6.29 (BGND), IC7.6 (GND_1), IC7.8 (GND_2), J1.5 (GND), J2.1, LED1.1 (K), R5.1, R8.1, R13.2, R14.1, U1.2 (GND), U2.2 (GND)
unnamed: IC2.6, R4.1
unnamed: IC3.12 (CS), R6.1
unnamed: IC4.4 (PR1), R7.1, R8.2
unnamed: IC4.8 (ST), R9.2, TP1.1
unnamed: IC6.28 (DTR), Q2.2 (E), R15.2
unnamed: IC6.9 (RSTB), R17.2
unnamed: IC6.24 (RTS), Q1.2 (E), R16.2
unnamed: C14.2, IC6.8 (VBUS), R12.1, R13.1
unnamed: C15.1, IC7.5 (C1)
unnamed: IC7.3 (CS), R18.2
unnamed: LED1.2 (A), R1.2
unnamed: LED2.1 (K), R14.2
unnamed: Q1.1 (B), R15.1
unnamed: Q2.1 (B), R16.1
unnamed: R10.2, U2.1 (I/O1)
unnamed: R11.2, U2.3 (I/O2)
unnamed: R5.2, U1.8 (Rs)
VBUS: C8.2, IC4.6 (VIN2), J1.1 (VBUS), R12.2, U2.5 (VBUS)
VCC: C7.2, IC4.3 (VIN1), IC4.5 (MODE), J2.2, R7.2

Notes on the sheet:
3.3V LDO
Mounting Holes
IIS2MDCTR
ESP_Programmer
Connectors
IMU
5v Mux
ESP32-S3-WROOM-1-N8R8
Power Regulators
CAN
ESP_PROG
CAN Transceiver

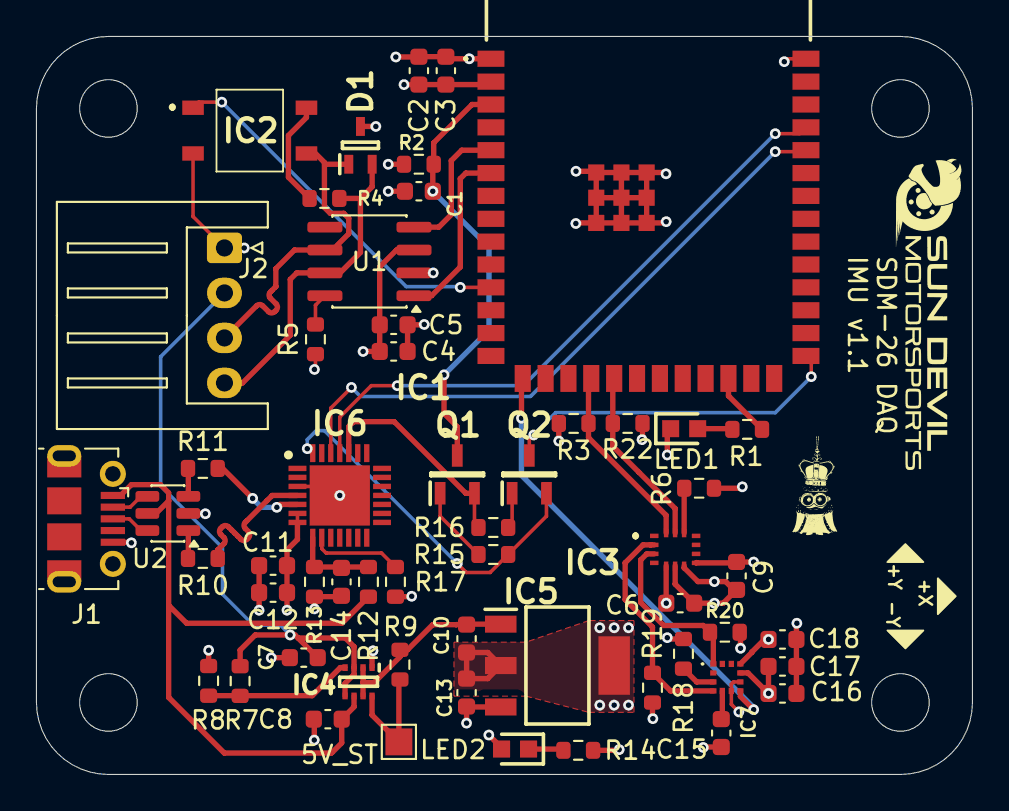
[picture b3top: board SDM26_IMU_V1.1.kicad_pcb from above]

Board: 4 copper layers, 52.0 x 41.0 mm, 60 parts (0 on the bottom side), 41 nets.
